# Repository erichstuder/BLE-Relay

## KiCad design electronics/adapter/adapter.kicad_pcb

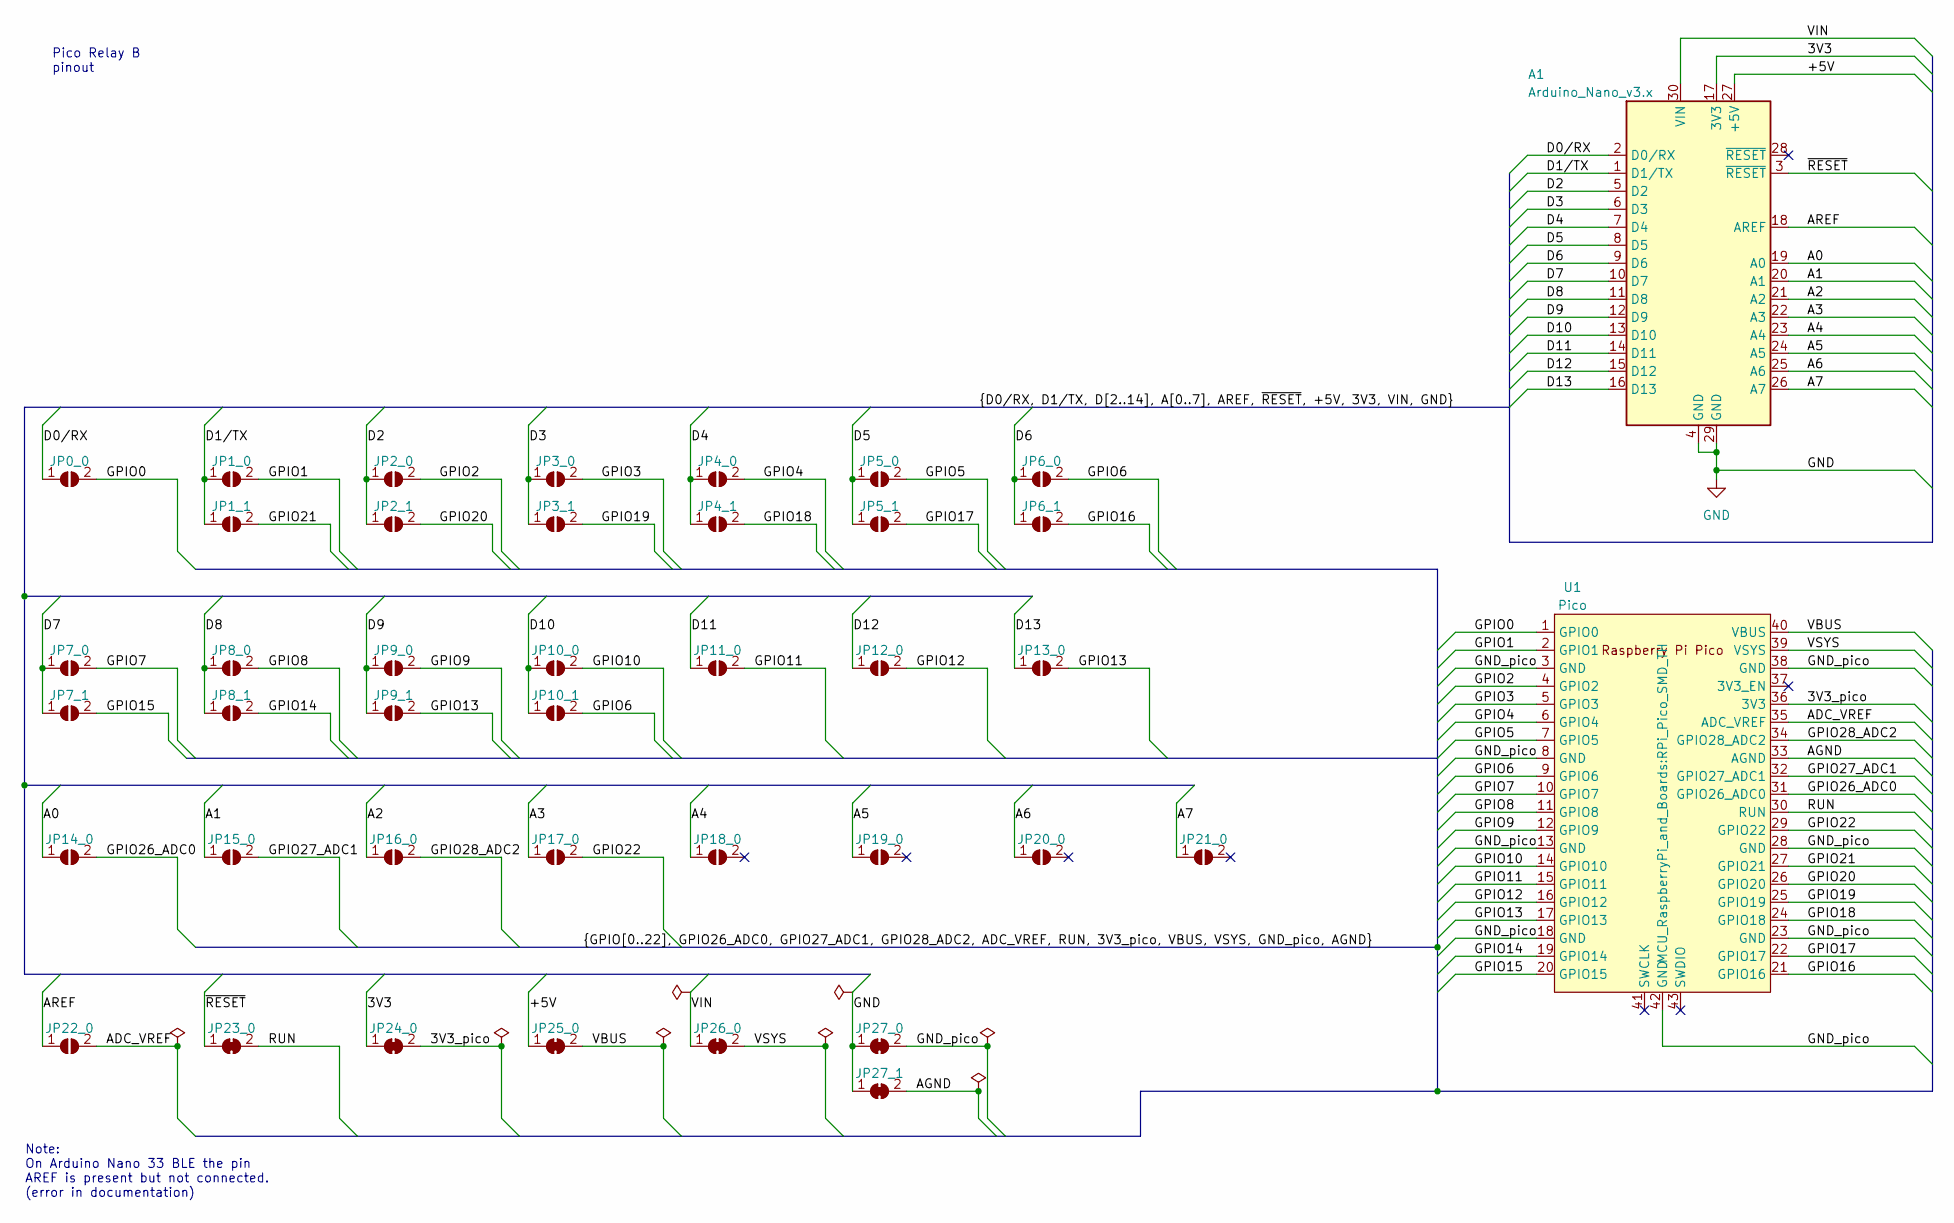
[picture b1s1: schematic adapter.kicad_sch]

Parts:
A1: Arduino_Nano_v3.x; Arduino_Nano_WithMountingHoles
JP0_0, JP1_0, JP1_1, JP2_0, JP2_1, JP3_0, JP3_1, JP4_0, JP4_1, JP5_0, JP5_1, JP6_0, JP6_1, JP7_0, JP7_1, JP8_0, JP8_1, JP9_0, JP9_1, JP10_0, JP10_1, JP11_0, JP12_0, JP13_0, JP14_0, JP15_0, JP16_0, JP17_0, JP18_0, JP19_0, JP20_0, JP21_0, JP22_0: SolderJumper_2_Open; SolderJumper-2_P1.3mm_Open_RoundedPad1.0x1.5mm
JP23_0, JP24_0, JP25_0, JP26_0, JP27_0, JP27_1: SolderJumper_2_Bridged; SolderJumper-2_P1.3mm_Bridged_RoundedPad1.0x1.5mm
U1: Pico; RPi_Pico_SMD_TH

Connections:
/3V3: A1.17 (3V3), JP24_0.1 (A)
/3V3_pico: JP24_0.2 (B), U1.36 (3V3)
/+5V: A1.27 (+5V), JP25_0.1 (A)
/A0: A1.19 (A0), JP14_0.1 (A)
/A1: A1.20 (A1), JP15_0.1 (A)
/A2: A1.21 (A2), JP16_0.1 (A)
/A3: A1.22 (A3), JP17_0.1 (A)
/A4: A1.23 (A4), JP18_0.1 (A)
/A5: A1.24 (A5), JP19_0.1 (A)
/A6: A1.25 (A6), JP20_0.1 (A)
/A7: A1.26 (A7), JP21_0.1 (A)
/ADC_VREF: JP22_0.2 (B), U1.35 (ADC_VREF)
/AGND: JP27_1.2 (B), U1.33 (AGND)
/AREF: A1.18 (AREF), JP22_0.1 (A)
/D0/RX: A1.2 (D0/RX), JP0_0.1 (A)
/D1/TX: A1.1 (D1/TX), JP1_0.1 (A), JP1_1.1 (A)
/D2: A1.5 (D2), JP2_0.1 (A), JP2_1.1 (A)
/D3: A1.6 (D3), JP3_0.1 (A), JP3_1.1 (A)
/D4: A1.7 (D4), JP4_0.1 (A), JP4_1.1 (A)
/D5: A1.8 (D5), JP5_0.1 (A), JP5_1.1 (A)
/D6: A1.9 (D6), JP6_0.1 (A), JP6_1.1 (A)
/D7: A1.10 (D7), JP7_0.1 (A), JP7_1.1 (A)
/D8: A1.11 (D8), JP8_0.1 (A), JP8_1.1 (A)
/D9: A1.12 (D9), JP9_0.1 (A), JP9_1.1 (A)
/D10: A1.13 (D10), JP10_0.1 (A), JP10_1.1 (A)
/D11: A1.14 (D11), JP11_0.1 (A)
/D12: A1.15 (D12), JP12_0.1 (A)
/D13: A1.16 (D13), JP13_0.1 (A)
/GND_pico: JP27_0.2 (B), U1.3 (GND), U1.8 (GND), U1.13 (GND), U1.18 (GND), U1.23 (GND), U1.28 (GND), U1.38 (GND), U1.42 (GND)
/GPIO0: JP0_0.2 (B), U1.1 (GPIO0)
/GPIO1: JP1_0.2 (B), U1.2 (GPIO1)
/GPIO2: JP2_0.2 (B), U1.4 (GPIO2)
/GPIO3: JP3_0.2 (B), U1.5 (GPIO3)
/GPIO4: JP4_0.2 (B), U1.6 (GPIO4)
/GPIO5: JP5_0.2 (B), U1.7 (GPIO5)
/GPIO6: JP6_0.2 (B), JP10_1.2 (B), U1.9 (GPIO6)
/GPIO7: JP7_0.2 (B), U1.10 (GPIO7)
/GPIO8: JP8_0.2 (B), U1.11 (GPIO8)
/GPIO9: JP9_0.2 (B), U1.12 (GPIO9)
/GPIO10: JP10_0.2 (B), U1.14 (GPIO10)
/GPIO11: JP11_0.2 (B), U1.15 (GPIO11)
/GPIO12: JP12_0.2 (B), U1.16 (GPIO12)
/GPIO13: JP9_1.2 (B), JP13_0.2 (B), U1.17 (GPIO13)
/GPIO14: JP8_1.2 (B), U1.19 (GPIO14)
/GPIO15: JP7_1.2 (B), U1.20 (GPIO15)
/GPIO16: JP6_1.2 (B), U1.21 (GPIO16)
/GPIO17: JP5_1.2 (B), U1.22 (GPIO17)
/GPIO18: JP4_1.2 (B), U1.24 (GPIO18)
/GPIO19: JP3_1.2 (B), U1.25 (GPIO19)
/GPIO20: JP2_1.2 (B), U1.26 (GPIO20)
/GPIO21: JP1_1.2 (B), U1.27 (GPIO21)
/GPIO22: JP17_0.2 (B), U1.29 (GPIO22)
/GPIO26_ADC0: JP14_0.2 (B), U1.31 (GPIO26_ADC0)
/GPIO27_ADC1: JP15_0.2 (B), U1.32 (GPIO27_ADC1)
/GPIO28_ADC2: JP16_0.2 (B), U1.34 (GPIO28_ADC2)
/RUN: JP23_0.2 (B), U1.30 (RUN)
/VBUS: JP25_0.2 (B), U1.40 (VBUS)
/VIN: A1.30 (VIN), JP26_0.1 (A)
/VSYS: JP26_0.2 (B), U1.39 (VSYS)
/~RESET: A1.3 (~RESET), JP23_0.1 (A)
GND: A1.4 (GND), A1.29 (GND), JP27_0.1 (A), JP27_1.1 (A)

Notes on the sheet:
Note: On Arduino Nano 33 BLE the pin AREF is present but not connected. (error in documentation)
Pico Relay B pinout

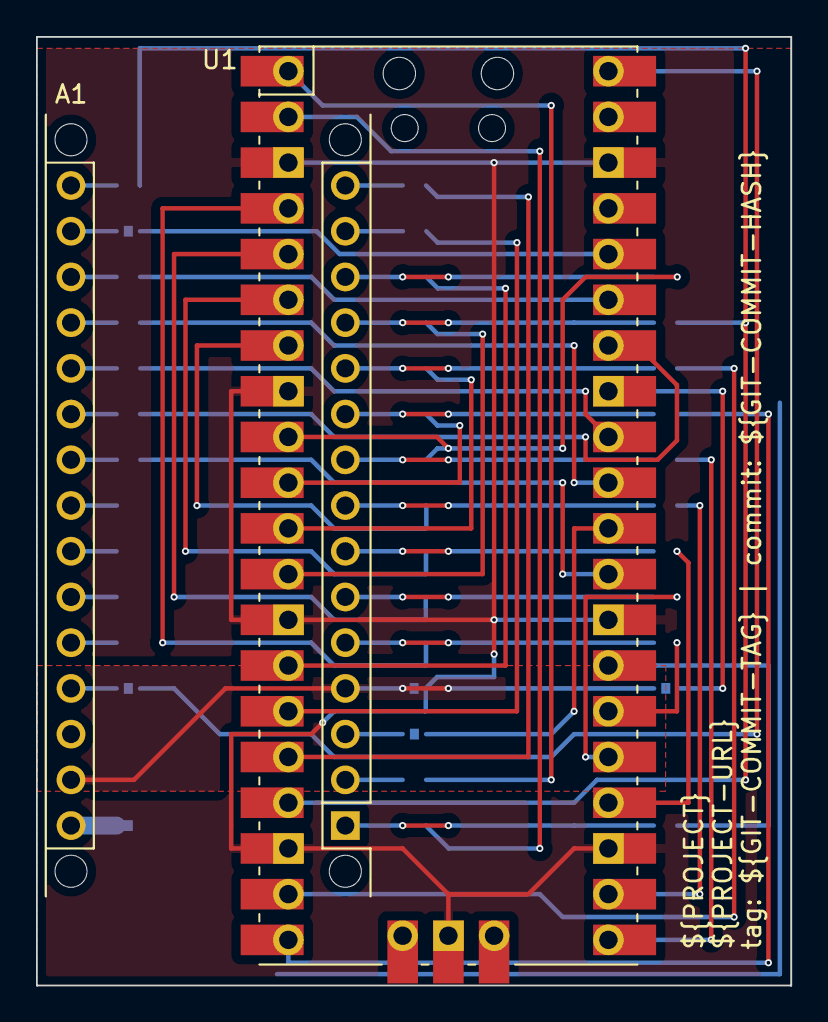
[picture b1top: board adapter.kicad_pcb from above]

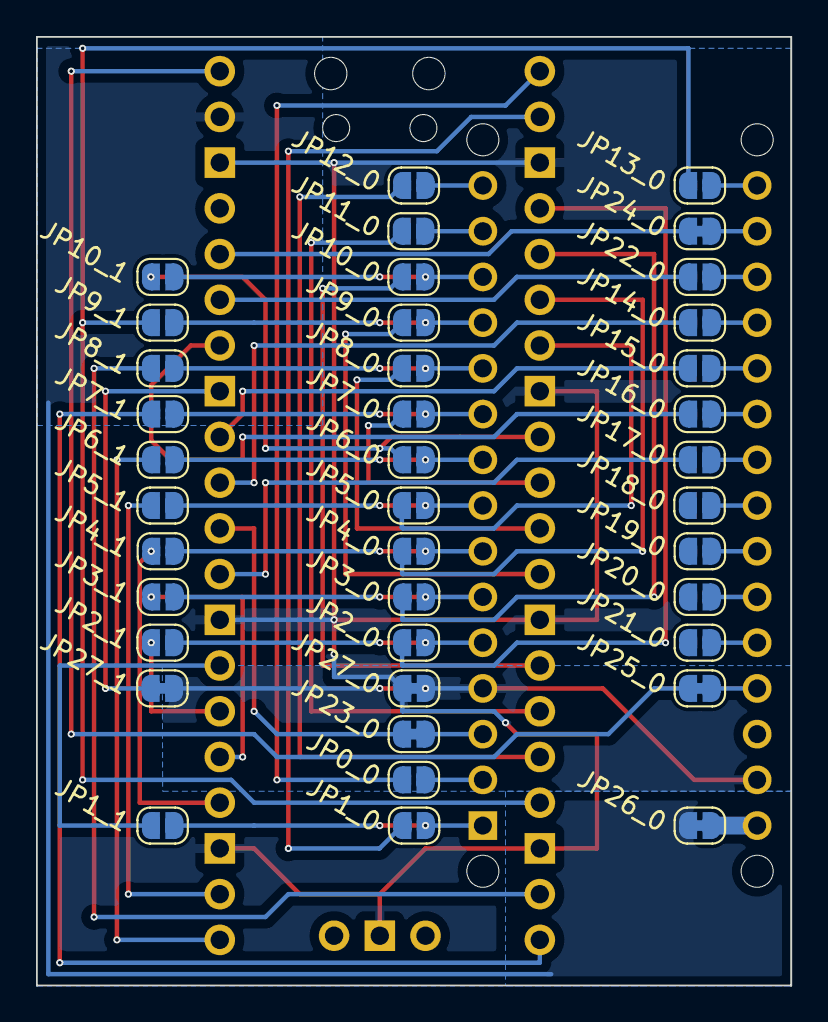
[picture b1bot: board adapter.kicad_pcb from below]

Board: 2 copper layers, 41.9 x 52.7 mm, 41 parts (39 on the bottom side), 61 nets.

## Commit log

2022-07-06 add arduino nano and rpi pico
2022-07-07 add Pico Relay B data
2022-07-07 add some connections and comments
2022-07-08 add connection matrix
2022-07-08 place components on pcb
2022-07-10 default closed solder jumpers, datasheets, erc
2022-07-10 route pcb
2022-07-11 add filled zones
2022-07-11 add workflow
2022-07-11 add variables for workflow
2022-07-11 correct typo in text variable
2022-07-11 rename electronics project
2022-07-11 add back silkscreen
2022-07-11 change the tag that triggers a release
2022-07-16 solve drc warning
2022-07-16 add adapter pcb
2022-07-16 bugfix
